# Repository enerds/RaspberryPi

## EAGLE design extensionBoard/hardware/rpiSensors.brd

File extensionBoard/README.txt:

=== Contents

== Hardware
The schematics and board layout of the extension board.
It is based on an atmega8 and currently on a breadboard.

== Software
This is the software that will run on the atmega8.
It already handles serial communication,
you can set input/output direction of a pin,
high/low value, and get ADC readings from all five channels.
Also, it pulses an LED wired to PB1 as a heartbeat.

== HostSoftware
This is meant to run on the Raspberry Pi, as a connection
between the web-interface and database and the atmega.
It will periodically check ifthenelse-triggers, read ADC
values to the database, and update pin definitions from the database.

=== Serial Commands Currently Implemented
== PXYZ - Set pin as in-/output
	X: B|C|D
	Y: 0-8
	Z: 1|0 (1=output,0=input)

== SXYZ - Set Pin H/L
	X: B|C|D
	Y: 0-8
	Z: 1|0 (1=H,0=L)

== GXY - Get ADC or digital Value of Pin
	X: B|C|D
	Y: 0-8

=== TODO
- Implement digital reading of pins in 'G'-Function
- Implement PWM functionality
- Extend HostSoftware

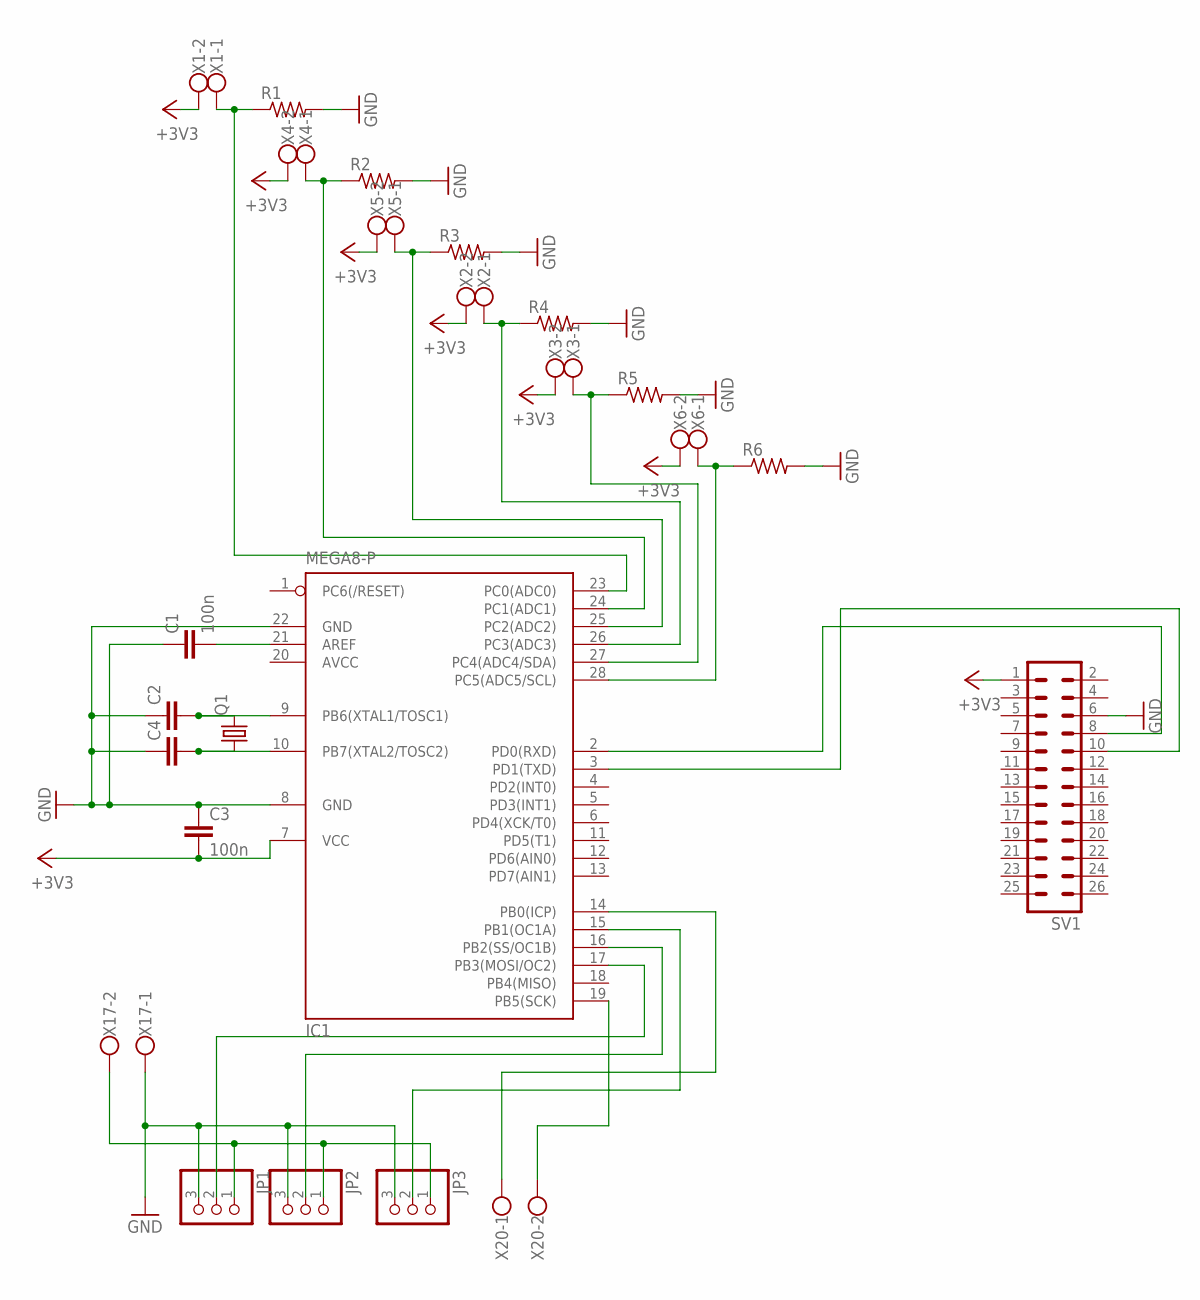
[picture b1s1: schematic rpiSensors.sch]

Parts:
C1, C3: 100n; C2.5-3
C2, C4: C5/2.5; C5B2.5
IC1: MEGA8-P; DIL28-3
JP1, JP2, JP3: PINHD-1X3; 1X03
Q1: CRYSTALHC49S; HC49/S
R1, R2, R3, R4, R5, R6: R-US_0309/12; 0309/12
SV1: ML26
X1, X2, X3, X4, X5, X6, X17, X20: W237-102

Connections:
+3V3: C3.2, IC1.7 (VCC), SV1.1, X1.2, X2.2, X3.2, X4.2, X5.2, X6.2
AVCC: IC1.20 (AVCC)
GND: C1.1, C2.1, C3.1, C4.1, IC1.8 (GND), IC1.22 (GND), JP1.3, JP2.3, JP3.3, R1.2, R2.2, R3.2, R4.2, R5.2, R6.2, SV1.6, X17.1
unnamed: IC1.2 (PD0(RXD)), SV1.8
unnamed: IC1.3 (PD1(TXD)), SV1.10
unnamed: IC1.23 (PC0(ADC0)), R1.1, X1.1
unnamed: IC1.24 (PC1(ADC1)), R2.1, X4.1
unnamed: IC1.27 (PC4(ADC4/SDA)), R5.1, X3.1
unnamed: IC1.25 (PC2(ADC2)), R3.1, X5.1
unnamed: IC1.26 (PC3(ADC3)), R4.1, X2.1
unnamed: IC1.28 (PC5(ADC5/SCL)), R6.1, X6.1
unnamed: IC1.17 (PB3(MOSI/OC2)), JP1.2
unnamed: IC1.16 (PB2(SS/OC1B)), JP2.2
unnamed: IC1.15 (PB1(OC1A)), JP3.2
unnamed: IC1.19 (PB5(SCK)), X20.2
unnamed: IC1.14 (PB0(ICP)), X20.1
unnamed: C1.2, IC1.21 (AREF)
unnamed: JP1.1, JP2.1, JP3.1, X17.2
unnamed: C2.2, IC1.9 (PB6(XTAL1/TOSC1)), Q1.2
unnamed: C4.2, IC1.10 (PB7(XTAL2/TOSC2)), Q1.1

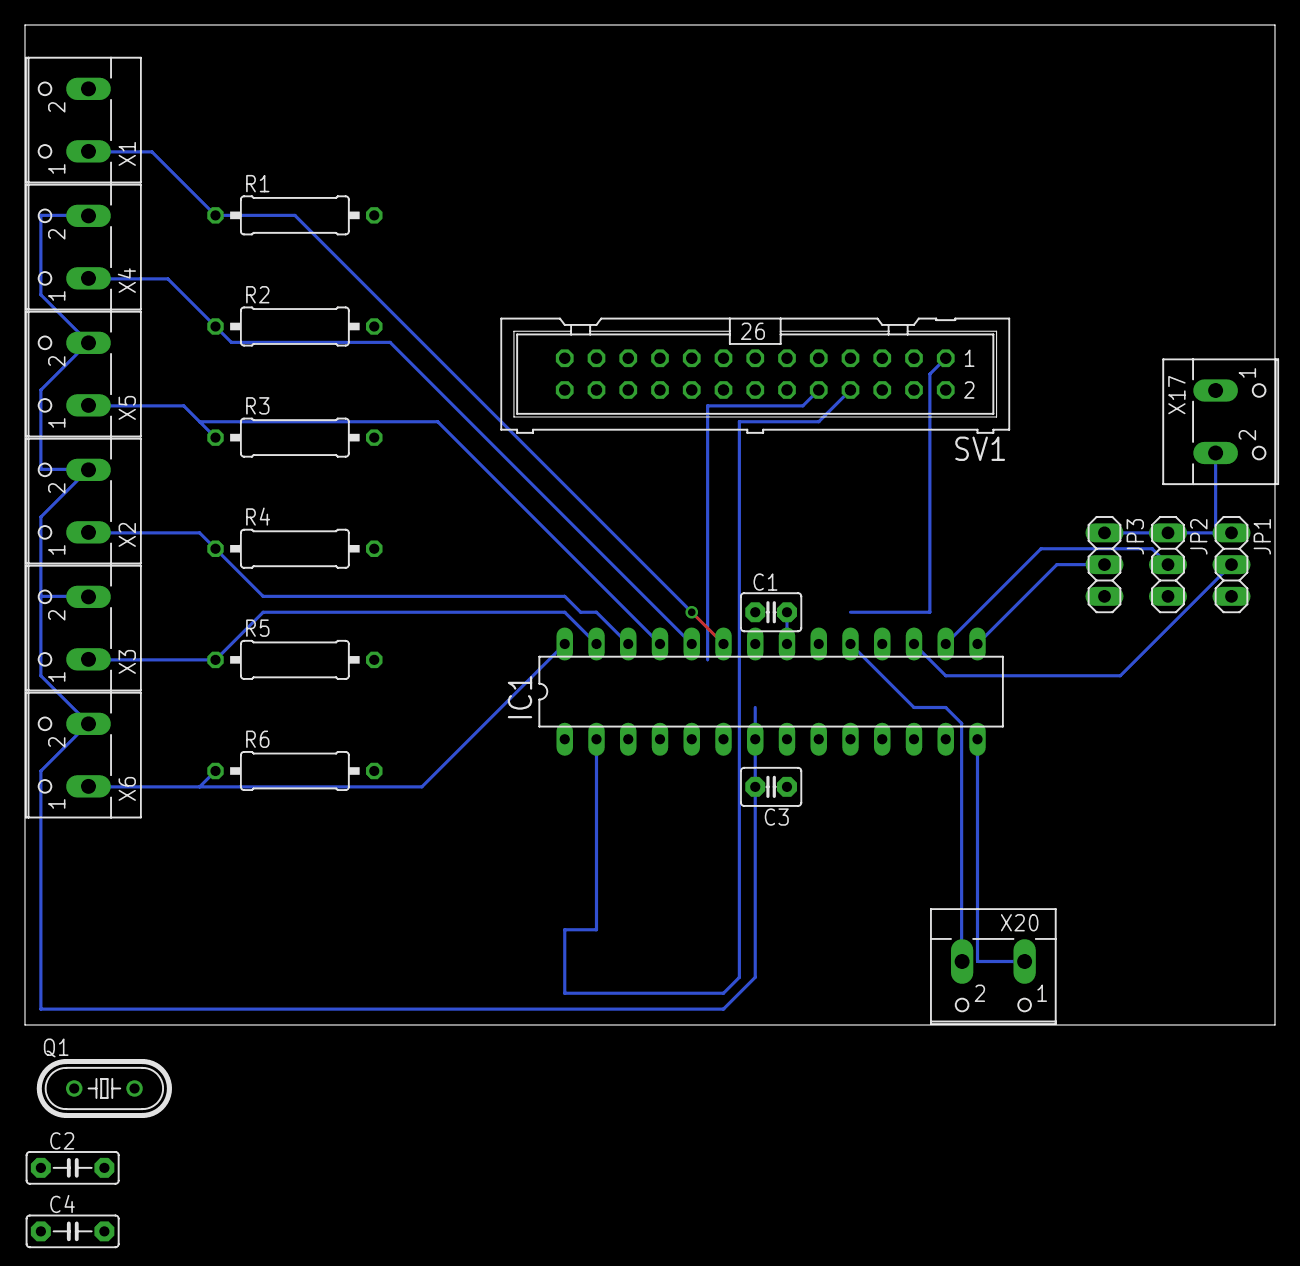
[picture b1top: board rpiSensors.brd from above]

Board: 2 copper layers, 100.0 x 80.0 mm, 24 parts (0 on the bottom side), 19 nets.

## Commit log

2012-05-24 added wiringPi, pinset code and ajax-site-stuff
2012-05-24 removed unused jquery libs
2012-05-25 added new printable files with cutout for flat ribbon extension cable
2012-05-29 added extension board schematics and board layout
2012-05-29 changed path
2012-05-29 minor
2012-06-01 added first uart example for the atmega to communicate with rpi
2012-06-01 adapted to new pin-setting procedures
2012-06-04 added newest printable files
2012-06-04 adc conversion and c-prog to get values via uart
2012-06-06 switches for external quarz
2012-06-06 corrected fusebits
2012-06-12 added steckdosenfunction
2012-06-12 changed delay, power outlet receiver works now
2012-07-27 New stuff
2012-10-04 test
2012-10-04 removed unused
2012-10-04 Added RFID reading daemon
2012-10-04 removed wiringPi, unused
2012-10-04 updated web frontend
2012-10-05 added sql and logger classes, implemented adc getter
2012-10-05 new table sensors for values. new field interval for adc intervals. implemented adc reading and intervals in hostSoftware
2012-10-05 clear response vector to get fresh values
2012-10-06 integrated new graphing library
2012-10-07 implemented fetching of PC0 data with ajax and dynamic redraw with jqplot
2012-10-07 minor changes on plot
2012-10-08 crazy php/js stuff to get all adcs plotted with correct replot functions
2012-10-08 auto-update for graphs
2012-10-09 dont connect database every single time, fixed memory leak
2012-10-09 removed points for every datapoint, added xticklabels to datapoints
2012-10-11 minor improvements over gui, autoupdating graphs and meaningful labels, minimal range selections
2012-10-11 revived schematics
2012-10-14 bash skript for speech synthesis with mbrola
2012-10-20 added library for 1.8 spi lcd display for atmega. based on arduino library
2012-10-21 added gfx functions, adapted from adafruit stuff, added rotation to draw text stuff
2012-10-21 included 1.8 spi lcd lib
